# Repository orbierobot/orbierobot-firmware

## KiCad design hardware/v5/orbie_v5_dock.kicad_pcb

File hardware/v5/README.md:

# Orbie V5 electronics (review package)

**Start with `Orbie_V5_Hardware_Review.pdf`** — what was done, how, and the checklist to verify.

| Board | Project | Fab files |
|---|---|---|
| Body controller r0.2 (retrofits the V3 body; outline to be confirmed, see PDF §6) | `orbie_v5_body.kicad_pro` | `out/orbie_v5_body_gerbers.zip`, `_pos.csv`, `_bom_jlc.csv` |
| Belly pogo pad r0.1 | `orbie_v5_pogo.kicad_pro` | `out/orbie_v5_pogo_*` |
| Dock base r0.1 (XIAO ESP32-C3, dead-until-docked pads, IR beacon, feeder/pump driver) | `orbie_v5_dock.kicad_pro` | `out/orbie_v5_dock_*` |
| Feeder module r0.1 | `orbie_v5_feeder.kicad_pro` | `out/orbie_v5_feeder_*` |
| Water module r0.1 | `orbie_v5_water.kicad_pro` | `out/orbie_v5_water_*` |

All five: KiCad 10, 2-layer, autorouted (freerouting), ERC 0 / DRC 0 (`out/*.erc.json`, `out/*.drc.json`).

## Regenerating
The boards are generated from `gen_v5.py` (placement + netlist) using the stock KiCad 10 libraries, then routed by `route_v5.py`:

```
KPY=/Applications/KiCad/KiCad.app/Contents/Frameworks/Python.framework/Versions/3.9/bin/python3
$KPY gen_v5.py . body        # or dock | feeder | water | pogo | all
FREEROUTING=/Applications/freerouting.app/Contents/MacOS/freerouting $KPY route_v5.py orbie_v5_body.kicad_pcb --passes 60
```
Edit the generator, not the outputs. Licence: CERN-OHL-S-2.0.

## Status
Hardware only. Not yet written: RP2040 balance firmware (`orbie_motion`), dock ESP32-C3 firmware, head-side ESP-IDF changes (UART to body on GPIO1/2, IR RMT on GPIO3, lidar UART on GPIO4).

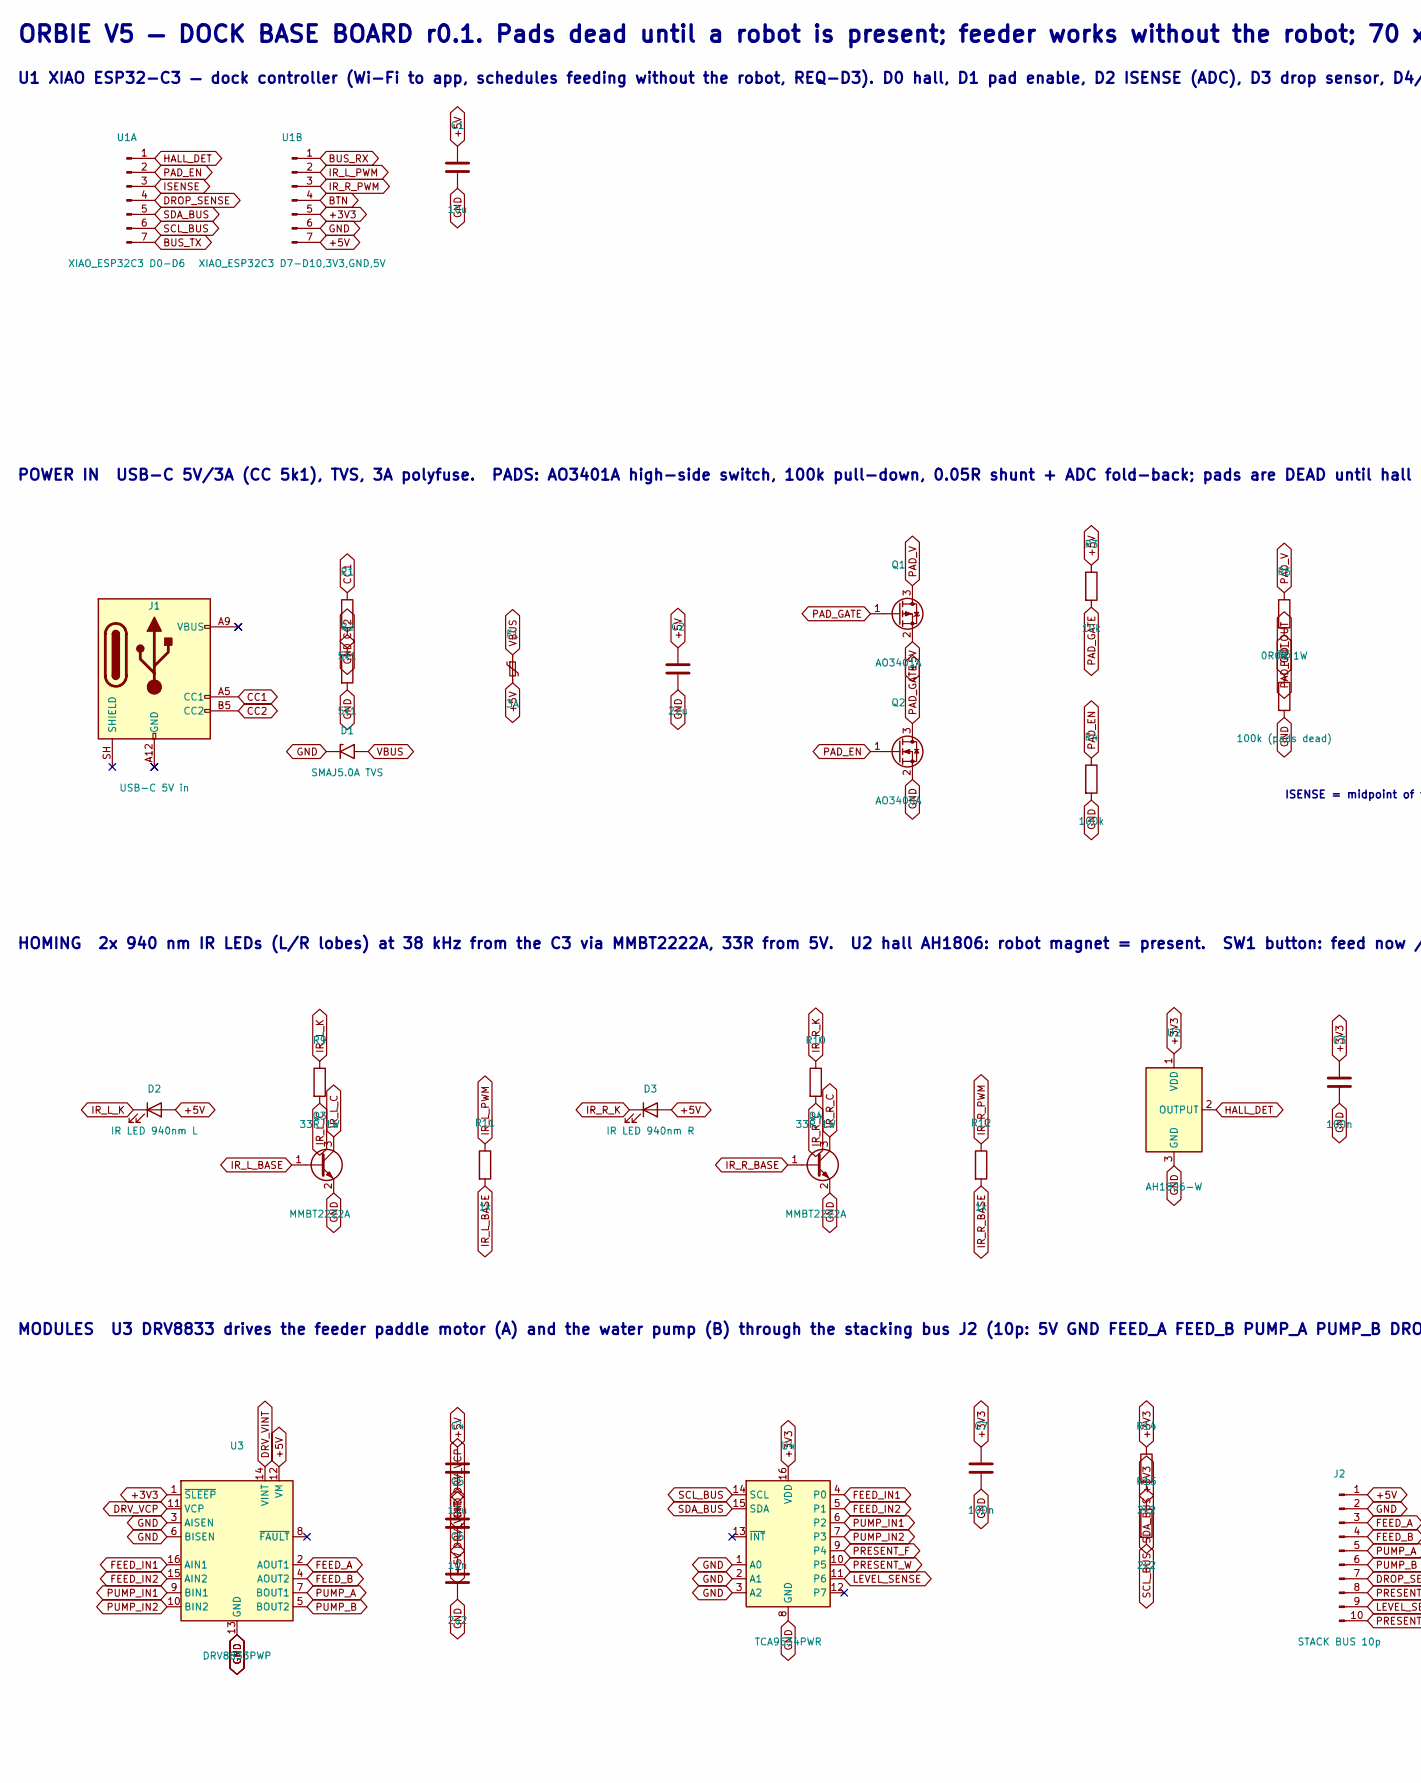
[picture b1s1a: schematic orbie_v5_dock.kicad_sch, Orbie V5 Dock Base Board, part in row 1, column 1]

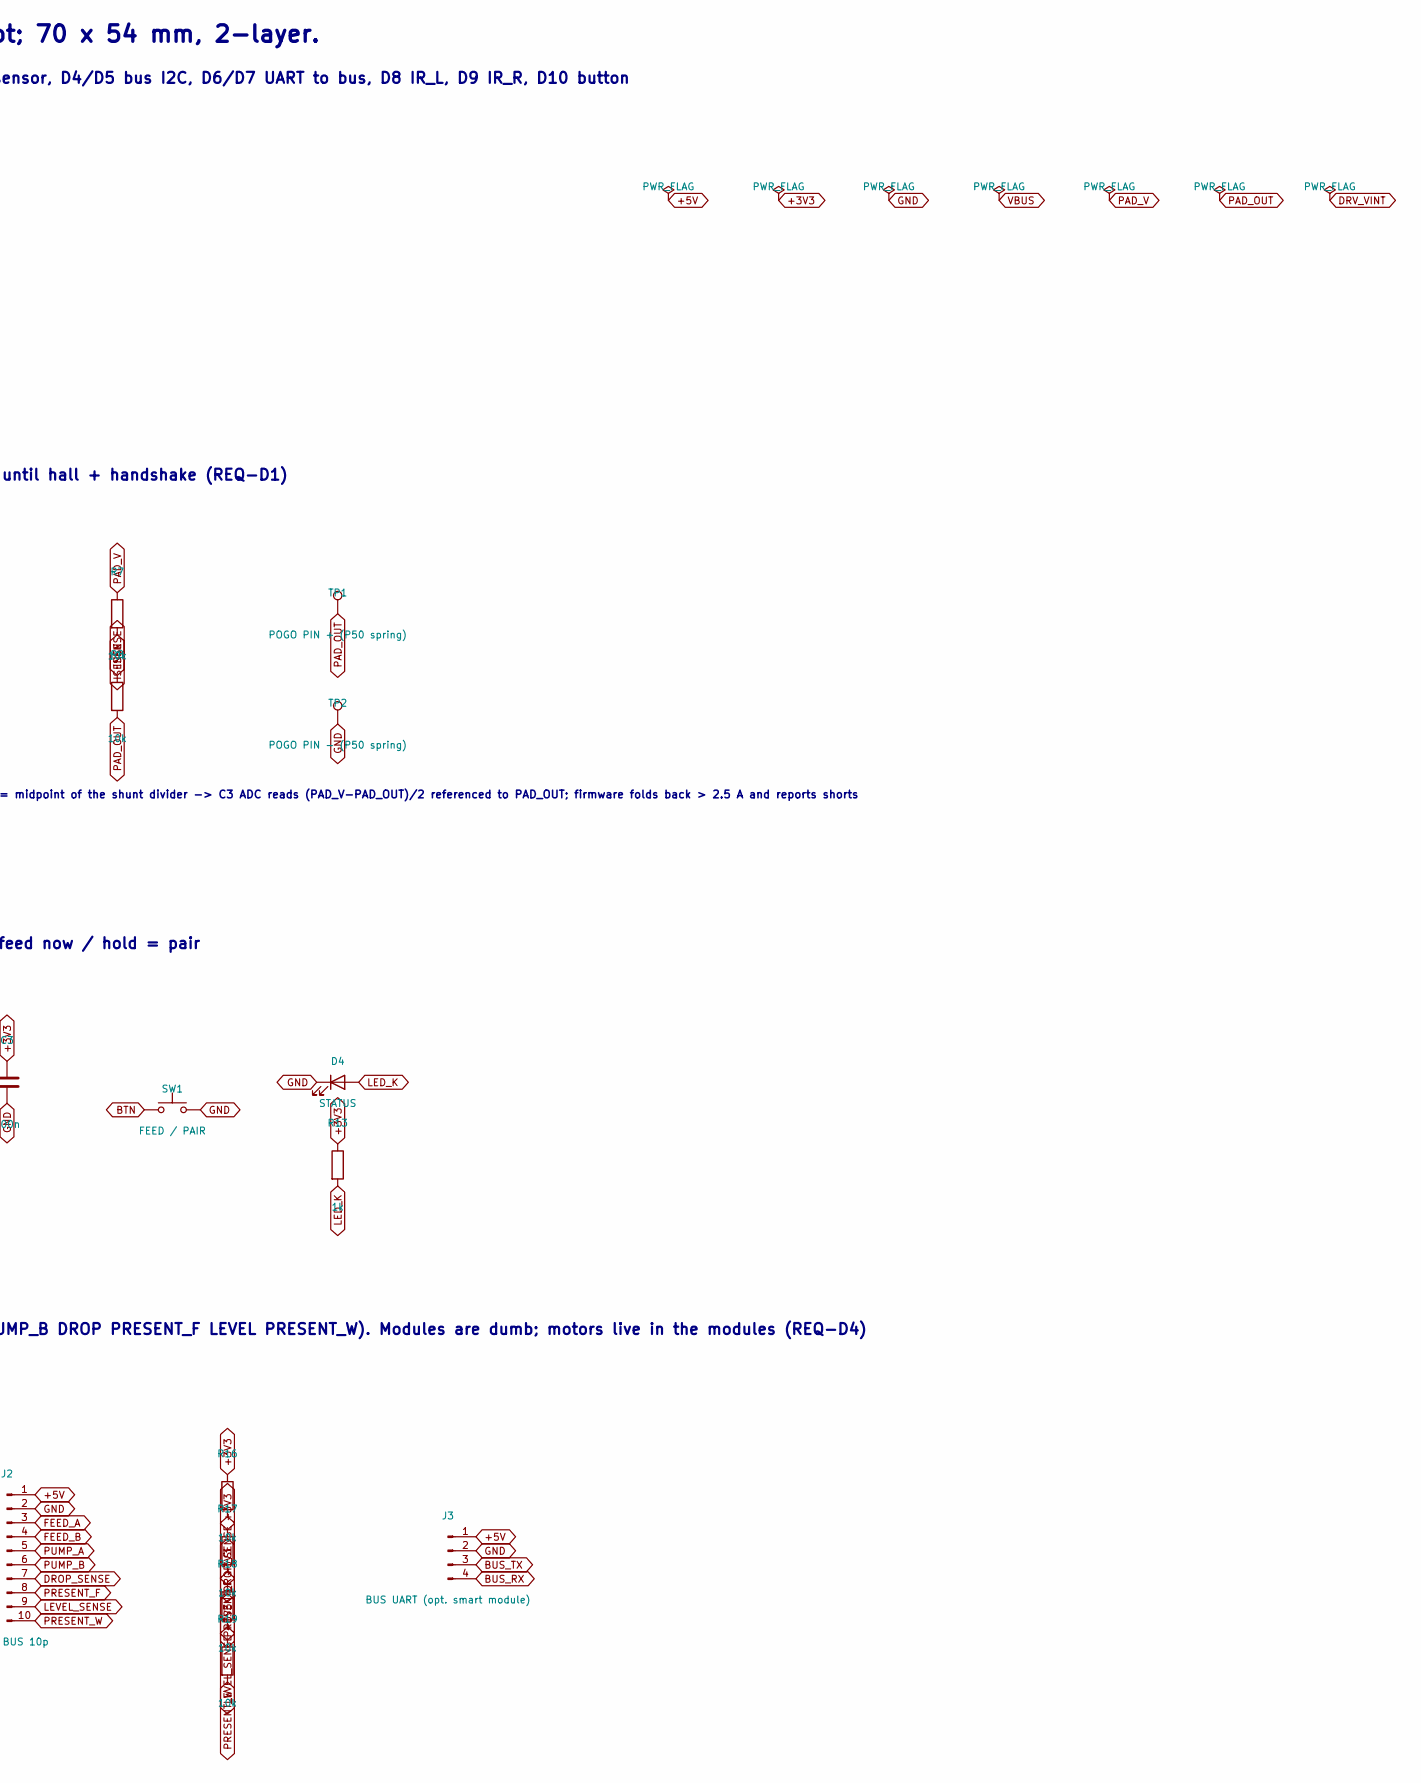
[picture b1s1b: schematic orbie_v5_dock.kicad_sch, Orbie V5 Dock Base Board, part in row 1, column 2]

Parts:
C1, C4: 10u; C_0805_2012Metric_Pad1.18x1.45mm_HandSolder
C2: 22u; C_1210_3225Metric_Pad1.33x2.70mm_HandSolder
C3, C7: 100n; C_0603_1608Metric_Pad1.08x0.95mm_HandSolder
C5: 10n; C_0603_1608Metric_Pad1.08x0.95mm_HandSolder
C6: 2u2; C_0603_1608Metric_Pad1.08x0.95mm_HandSolder
D1: SMAJ5.0A TVS; D_SMA
D2: IR LED 940nm L; LED_D5.0mm
D3: IR LED 940nm R; LED_D5.0mm
D4: STATUS; LED_0603_1608Metric
F1: 3A; Fuse_1206_3216Metric
J1: USB-C 5V in; USB_C_Receptacle_GCT_USB4125-xx-x_6P_TopMnt_Horizontal
J2: STACK BUS 10p; JST_PH_B10B-PH-K_1x10_P2.00mm_Vertical
J3: BUS UART (opt. smart module); JST_PH_B4B-PH-K_1x04_P2.00mm_Vertical
Q1: AO3401A; SOT-23_Handsoldering
Q2: AO3400A; SOT-23_Handsoldering
Q3, Q4: MMBT2222A; SOT-23_Handsoldering
R1, R2: 5k1; R_0603_1608Metric_Pad0.98x0.95mm_HandSolder
R3, R7, R8, R16, R17, R18, R19: 10k; R_0603_1608Metric_Pad0.98x0.95mm_HandSolder
R4: 100k; R_0603_1608Metric_Pad0.98x0.95mm_HandSolder
R5: 0R05 1W; R_2512_6332Metric
R6: 100k (pads dead); R_0603_1608Metric_Pad0.98x0.95mm_HandSolder
R9, R10: 33R 1W; R_1206_3216Metric
R11, R12, R13: 1k; R_0603_1608Metric_Pad0.98x0.95mm_HandSolder
R14, R15: 2k2; R_0603_1608Metric_Pad0.98x0.95mm_HandSolder
SW1: FEED / PAIR; SW_Push_1P1T_NO_CK_KMR2
TP1: POGO PIN + (P50 spring); TestPoint_THTPad_D2.0mm_Drill1.0mm
TP2: POGO PIN - (P50 spring); TestPoint_THTPad_D2.0mm_Drill1.0mm
U1A: XIAO_ESP32C3 D0-D6; XIAO_Castellated
U1B: XIAO_ESP32C3 D7-D10,3V3,GND,5V; XIAO_Castellated
U2: AH1806-W; SOT-23_Handsoldering
U3: DRV8833PWP; HTSSOP-16-1EP_4.4x5mm_P0.65mm_EP3.4x5mm
U4: TCA9534PWR; TSSOP-16_4.4x5mm_P0.65mm

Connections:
+3V3: C3.1, C7.1, R13.1, R14.1, R15.1, R16.1, R17.1, R18.1, R19.1, U1A.12, U1B.5, U2.1 (VDD), U3.1 (~SLEEP), U4.16 (VDD)
+5V: C1.1, C2.1, C4.1, C5.2, D2.2 (A), D3.2 (A), F1.2, J2.1, J3.1, Q1.2 (S), R3.1, U1A.14, U1B.7, U3.12 (VM)
BTN: SW1.1, U1A.11, U1B.4
BUS_RX: J3.4, U1A.8, U1B.1
BUS_TX: J3.3, U1A.7
CC1: J1.A5 (CC1), R1.1
CC2: J1.B5 (CC2), R2.1
DROP_SENSE: J2.7, R16.2, U1A.4
DRV_VCP: C5.1, U3.11 (VCP)
DRV_VINT: C6.1, U3.14 (VINT)
FEED_A: J2.3, U3.2 (AOUT1)
FEED_B: J2.4, U3.4 (AOUT2)
FEED_IN1: U3.16 (AIN1), U4.4 (P0)
FEED_IN2: U3.15 (AIN2), U4.5 (P1)
GND: C1.2, C2.2, C3.2, C4.2, C6.2, C7.2, D1.1 (A1), D4.1 (K), J2.2, J3.2, Q2.2 (S), Q3.2 (E), Q4.2 (E), R1.2, R2.2, R4.2, R6.2, SW1.2, TP2.1, U1A.13, U1B.6, U2.3 (GND), U3.3 (AISEN), U3.6 (BISEN), U3.13 (GND), U3.17 (GND), U4.1 (A0), U4.2 (A1), U4.3 (A2), U4.8 (GND)
HALL_DET: U1A.1, U2.2 (OUTPUT)
IR_L_BASE: Q3.1 (B), R11.2
IR_L_C: Q3.3 (C), R9.2
IR_L_K: D2.1 (K), R9.1
IR_L_PWM: R11.1, U1A.9, U1B.2
IR_R_BASE: Q4.1 (B), R12.2
IR_R_C: Q4.3 (C), R10.2
IR_R_K: D3.1 (K), R10.1
IR_R_PWM: R12.1, U1A.10, U1B.3
ISENSE: R7.2, R8.1, U1A.3
LED_K: D4.2 (A), R13.2
LEVEL_SENSE: J2.9, R18.2, U4.11 (P6)
PAD_EN: Q2.1 (G), R4.1, U1A.2
PAD_GATE: Q1.1 (G), Q2.3 (D), R3.2
PAD_OUT: R5.2, R6.1, R8.2, TP1.1
PAD_V: Q1.3 (D), R5.1, R7.1
PRESENT_F: J2.8, R17.2, U4.9 (P4)
PRESENT_W: J2.10, R19.2, U4.10 (P5)
PUMP_A: J2.5, U3.7 (BOUT1)
PUMP_B: J2.6, U3.5 (BOUT2)
PUMP_IN1: U3.9 (BIN1), U4.6 (P2)
PUMP_IN2: U3.10 (BIN2), U4.7 (P3)
SCL_BUS: R15.2, U1A.6, U4.14 (SCL)
SDA_BUS: R14.2, U1A.5, U4.15 (SDA)
VBUS: D1.2 (A2), F1.1

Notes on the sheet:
ORBIE V5 — DOCK BASE BOARD r0.1. Pads dead until a robot is present; feeder works without the robot; 70 x 54 mm, 2-layer.
U1 XIAO ESP32-C3 — dock controller (Wi-Fi to app, schedules feeding without the robot, REQ-D3). D0 hall, D1 pad enable, D2 ISENSE (ADC), D3 drop sensor, D4/D5 bus I2C, D6/D7 UART to bus, D8 IR_L, D9 IR_R, D10 button
POWER IN USB-C 5V/3A (CC 5k1), TVS, 3A polyfuse. PADS: AO3401A high-side switch, 100k pull-down, 0.05R shunt + ADC fold-back; pads are DEAD until hall + handshake (REQ-D1)
ISENSE = midpoint of the shunt divider -> C3 ADC reads (PAD_V-PAD_OUT)/2 referenced to PAD_OUT; firmware folds back > 2.5 A and reports shorts
HOMING 2x 940 nm IR LEDs (L/R lobes) at 38 kHz from the C3 via MMBT2222A, 33R from 5V. U2 hall AH1806: robot magnet = present. SW1 button: feed now / hold = pair
MODULES U3 DRV8833 drives the feeder paddle motor (A) and the water pump (B) through the stacking bus J2 (10p: 5V GND FEED_A FEED_B PUMP_A PUMP_B DROP PRESENT_F LEVEL PRESENT_W). Modules are dumb; motors live in the modules (REQ-D4)

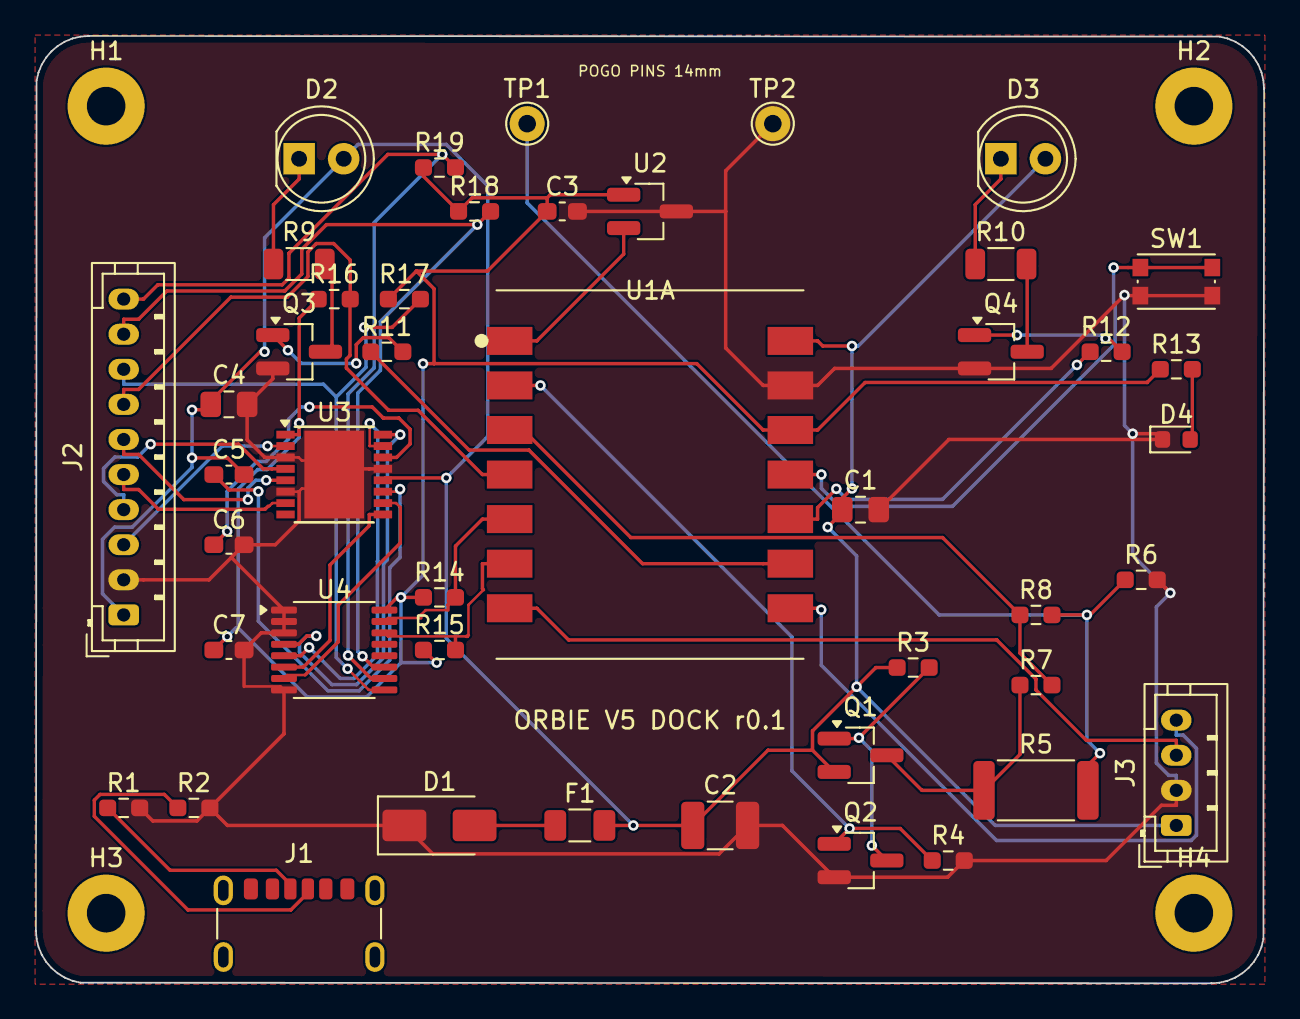
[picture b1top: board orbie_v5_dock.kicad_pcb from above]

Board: 2 copper layers, 70.0 x 54.0 mm, 49 parts (0 on the bottom side), 40 nets.

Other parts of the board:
H1, H2, H3, H4: MountingHole_2.2mm_M2_Pad

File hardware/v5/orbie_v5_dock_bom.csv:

Ref,Value,Symbol,Footprint,Side,Description
U1A,"XIAO_ESP32C3 D0-D6",Connector:Conn_01x07_Pin,orbie_v5:XIAO_Castellated,F,"XIAO ESP32-C3 left row"
U1B,"XIAO_ESP32C3 D7-D10,3V3,GND,5V",Connector:Conn_01x07_Pin,orbie_v5:XIAO_Castellated,F,"XIAO ESP32-C3 right row"
C1,"10u",Device:C,Capacitor_SMD:C_0805_2012Metric_Pad1.18x1.45mm_HandSolder,F,"capacitor"
J1,"USB-C 5V in",Connector:USB_C_Receptacle_PowerOnly_6P,Connector_USB:USB_C_Receptacle_GCT_USB4125-xx-x_6P_TopMnt_Horizontal,F,"USB-C 6P"
R1,"5k1",Device:R,Resistor_SMD:R_0603_1608Metric_Pad0.98x0.95mm_HandSolder,F,"resistor"
R2,"5k1",Device:R,Resistor_SMD:R_0603_1608Metric_Pad0.98x0.95mm_HandSolder,F,"resistor"
D1,"SMAJ5.0A TVS",Diode:SMAJ5.0A,Diode_SMD:D_SMA,F,""
F1,"3A",Device:Polyfuse_Small,Fuse:Fuse_1206_3216Metric,F,""
C2,"22u",Device:C,Capacitor_SMD:C_1210_3225Metric_Pad1.33x2.70mm_HandSolder,F,"capacitor"
Q1,"AO3401A",Transistor_FET:AO3401A,Package_TO_SOT_SMD:SOT-23_Handsoldering,F,"pad high-side switch"
Q2,"AO3400A",Transistor_FET:AO3400A,Package_TO_SOT_SMD:SOT-23_Handsoldering,F,"level shift"
R3,"10k",Device:R,Resistor_SMD:R_0603_1608Metric_Pad0.98x0.95mm_HandSolder,F,"resistor"
R4,"100k",Device:R,Resistor_SMD:R_0603_1608Metric_Pad0.98x0.95mm_HandSolder,F,"resistor"
R5,"0R05 1W",Device:R,Resistor_SMD:R_2512_6332Metric,F,"resistor"
R6,"100k (pads dead)",Device:R,Resistor_SMD:R_0603_1608Metric_Pad0.98x0.95mm_HandSolder,F,"resistor"
R7,"10k",Device:R,Resistor_SMD:R_0603_1608Metric_Pad0.98x0.95mm_HandSolder,F,"resistor"
R8,"10k",Device:R,Resistor_SMD:R_0603_1608Metric_Pad0.98x0.95mm_HandSolder,F,"resistor"
TP1,"POGO PIN + (P50 spring)",Connector:TestPoint,TestPoint:TestPoint_THTPad_D2.0mm_Drill1.0mm,F,"spring pin, 14 mm pitch"
TP2,"POGO PIN - (P50 spring)",Connector:TestPoint,TestPoint:TestPoint_THTPad_D2.0mm_Drill1.0mm,F,"spring pin"
D2,"IR LED 940nm L",Device:LED,LED_THT:LED_D5.0mm,F,"beacon lobe"
R9,"33R 1W",Device:R,Resistor_SMD:R_1206_3216Metric,F,"resistor"
Q3,"MMBT2222A",Transistor_BJT:MMBT2222A,Package_TO_SOT_SMD:SOT-23_Handsoldering,F,"LED driver"
R11,"1k",Device:R,Resistor_SMD:R_0603_1608Metric_Pad0.98x0.95mm_HandSolder,F,"resistor"
D3,"IR LED 940nm R",Device:LED,LED_THT:LED_D5.0mm,F,"beacon lobe"
R10,"33R 1W",Device:R,Resistor_SMD:R_1206_3216Metric,F,"resistor"
Q4,"MMBT2222A",Transistor_BJT:MMBT2222A,Package_TO_SOT_SMD:SOT-23_Handsoldering,F,"LED driver"
R12,"1k",Device:R,Resistor_SMD:R_0603_1608Metric_Pad0.98x0.95mm_HandSolder,F,"resistor"
U2,"AH1806-W",Sensor_Magnetic:AH1806-W,Package_TO_SOT_SMD:SOT-23_Handsoldering,F,"hall: robot present"
C3,"100n",Device:C,Capacitor_SMD:C_0603_1608Metric_Pad1.08x0.95mm_HandSolder,F,"capacitor"
SW1,"FEED / PAIR",Switch:SW_Push,Button_Switch_SMD:SW_Push_1P1T_NO_CK_KMR2,F,"user button"
D4,"STATUS",Device:LED,LED_SMD:LED_0603_1608Metric,F,""
R13,"1k",Device:R,Resistor_SMD:R_0603_1608Metric_Pad0.98x0.95mm_HandSolder,F,"resistor"
U3,"DRV8833PWP",Driver_Motor:DRV8833PWP,Package_SO:HTSSOP-16-1EP_4.4x5mm_P0.65mm_EP3.4x5mm,F,"feeder + pump driver"
C4,"10u",Device:C,Capacitor_SMD:C_0805_2012Metric_Pad1.18x1.45mm_HandSolder,F,"capacitor"
C5,"10n",Device:C,Capacitor_SMD:C_0603_1608Metric_Pad1.08x0.95mm_HandSolder,F,"capacitor"
C6,"2u2",Device:C,Capacitor_SMD:C_0603_1608Metric_Pad1.08x0.95mm_HandSolder,F,"capacitor"
U4,"TCA9534PWR",Interface_Expansion:TCA9534,Package_SO:TSSOP-16_4.4x5mm_P0.65mm,F,"expander: motor inputs + module present"
C7,"100n",Device:C,Capacitor_SMD:C_0603_1608Metric_Pad1.08x0.95mm_HandSolder,F,"capacitor"
R14,"2k2",Device:R,Resistor_SMD:R_0603_1608Metric_Pad0.98x0.95mm_HandSolder,F,"resistor"
R15,"2k2",Device:R,Resistor_SMD:R_0603_1608Metric_Pad0.98x0.95mm_HandSolder,F,"resistor"
J2,"STACK BUS 10p",Connector:Conn_01x10_Pin,Connector_JST:JST_PH_B10B-PH-K_1x10_P2.00mm_Vertical,F,"to feeder / water modules (spring contacts on the deck)"
R16,"10k",Device:R,Resistor_SMD:R_0603_1608Metric_Pad0.98x0.95mm_HandSolder,F,"resistor"
R17,"10k",Device:R,Resistor_SMD:R_0603_1608Metric_Pad0.98x0.95mm_HandSolder,F,"resistor"
R18,"10k",Device:R,Resistor_SMD:R_0603_1608Metric_Pad0.98x0.95mm_HandSolder,F,"resistor"
R19,"10k",Device:R,Resistor_SMD:R_0603_1608Metric_Pad0.98x0.95mm_HandSolder,F,"resistor"
J3,"BUS UART (opt. smart module)",Connector:Conn_01x04_Pin,Connector_JST:JST_PH_B4B-PH-K_1x04_P2.00mm_Vertical,F,"optional"

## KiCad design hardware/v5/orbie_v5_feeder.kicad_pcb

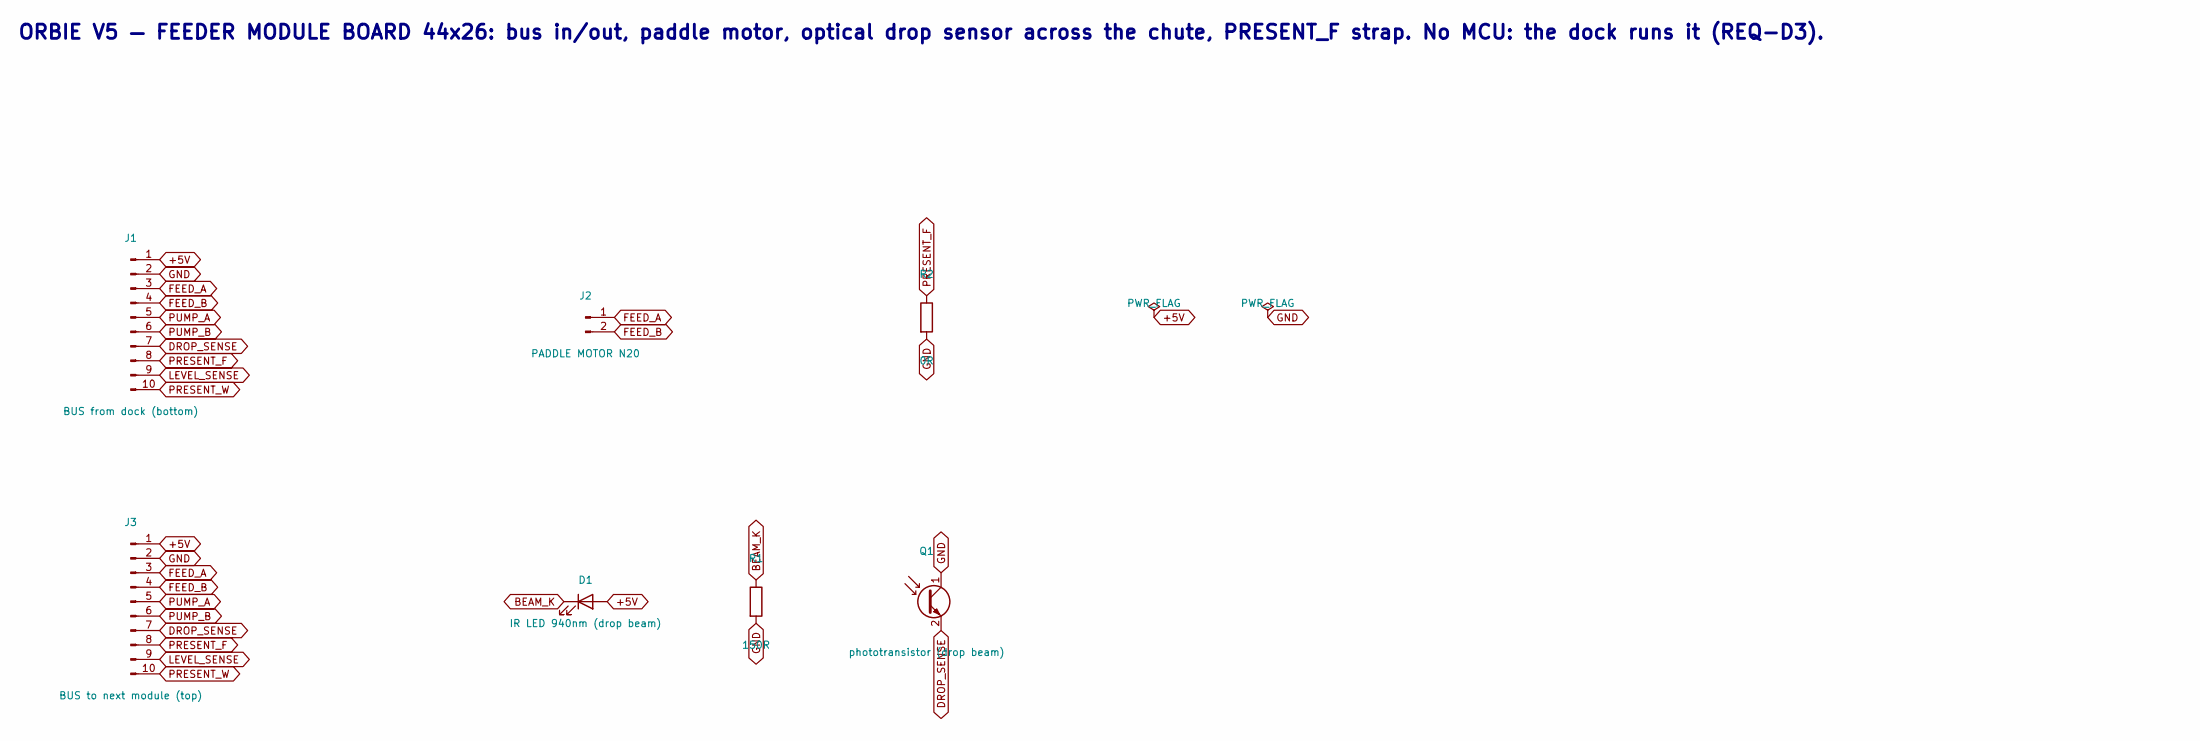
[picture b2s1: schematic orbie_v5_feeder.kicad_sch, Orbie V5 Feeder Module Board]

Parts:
D1: IR LED 940nm (drop beam); LED_D3.0mm
J1: BUS from dock (bottom); JST_PH_B10B-PH-K_1x10_P2.00mm_Vertical
J2: PADDLE MOTOR N20; JST_PH_B2B-PH-K_1x02_P2.00mm_Vertical
J3: BUS to next module (top); JST_PH_B10B-PH-K_1x10_P2.00mm_Vertical
Q1: phototransistor (drop beam); LED_D3.0mm
R1: 150R; R_0603_1608Metric_Pad0.98x0.95mm_HandSolder
R2: 0R; R_0603_1608Metric_Pad0.98x0.95mm_HandSolder

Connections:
+5V: D1.2 (A), J1.1, J3.1
BEAM_K: D1.1 (K), R1.1
DROP_SENSE: J1.7, J3.7, Q1.2 (E)
FEED_A: J1.3, J2.1, J3.3
FEED_B: J1.4, J2.2, J3.4
GND: J1.2, J3.2, Q1.1 (C), R1.2, R2.2
LEVEL_SENSE: J1.9, J3.9
PRESENT_F: J1.8, J3.8, R2.1
PRESENT_W: J1.10, J3.10
PUMP_A: J1.5, J3.5
PUMP_B: J1.6, J3.6

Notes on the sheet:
ORBIE V5 — FEEDER MODULE BOARD 44x26: bus in/out, paddle motor, optical drop sensor across the chute, PRESENT_F strap. No MCU: the dock runs it (REQ-D3).

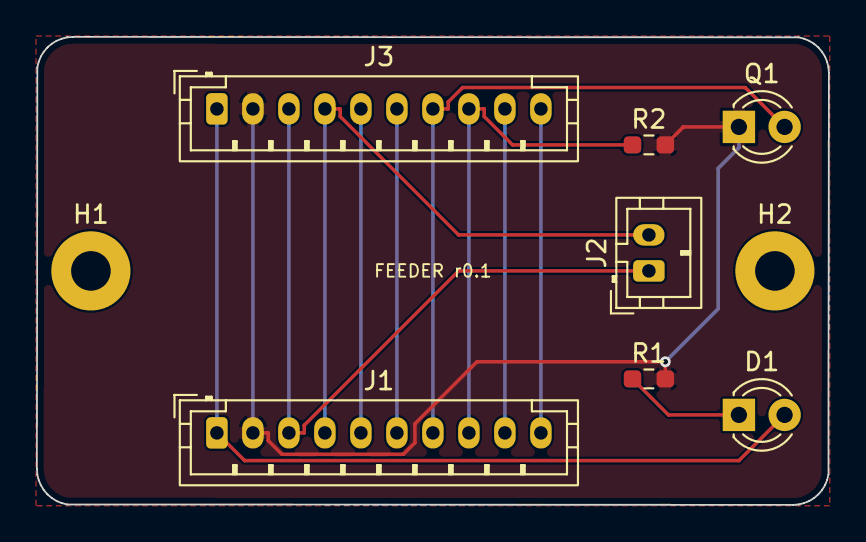
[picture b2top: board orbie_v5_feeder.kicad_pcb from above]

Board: 2 copper layers, 44.0 x 26.0 mm, 9 parts (0 on the bottom side), 11 nets.

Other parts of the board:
H1, H2: MountingHole_2.2mm_M2_Pad

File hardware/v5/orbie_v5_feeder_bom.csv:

Ref,Value,Symbol,Footprint,Side,Description
J1,"BUS from dock (bottom)",Connector:Conn_01x10_Pin,Connector_JST:JST_PH_B10B-PH-K_1x10_P2.00mm_Vertical,F,"spring-contact bus, bottom face"
J3,"BUS to next module (top)",Connector:Conn_01x10_Pin,Connector_JST:JST_PH_B10B-PH-K_1x10_P2.00mm_Vertical,F,"pass-through so the water tower stacks on top"
J2,"PADDLE MOTOR N20",Connector:Conn_01x02_Pin,Connector_JST:JST_PH_B2B-PH-K_1x02_P2.00mm_Vertical,F,"paddle drum gearmotor"
D1,"IR LED 940nm (drop beam)",Device:LED,LED_THT:LED_D3.0mm,F,"chute emitter"
R1,"150R",Device:R,Resistor_SMD:R_0603_1608Metric_Pad0.98x0.95mm_HandSolder,F,"resistor"
Q1,"phototransistor (drop beam)",Device:Q_Photo_NPN,LED_THT:LED_D3.0mm,F,"chute receiver, pulled up at the dock"
R2,"0R",Device:R,Resistor_SMD:R_0603_1608Metric_Pad0.98x0.95mm_HandSolder,F,"resistor"

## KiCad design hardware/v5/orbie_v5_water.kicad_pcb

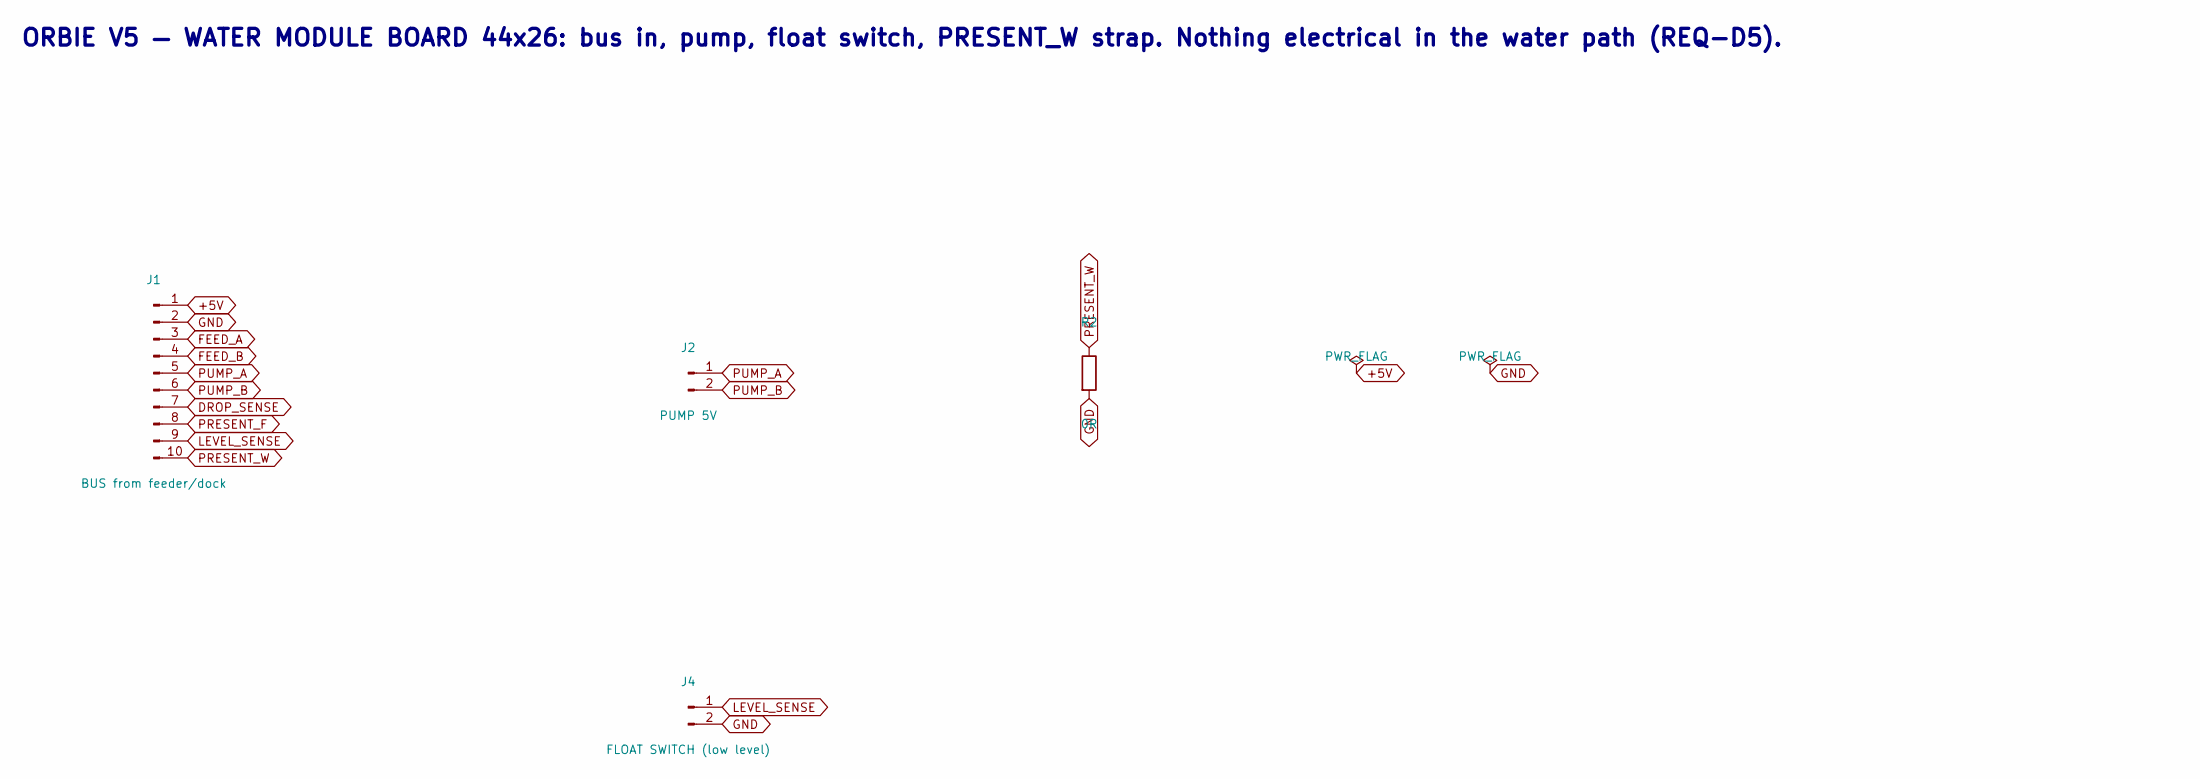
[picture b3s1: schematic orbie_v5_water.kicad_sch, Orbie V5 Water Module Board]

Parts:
J1: BUS from feeder/dock; JST_PH_B10B-PH-K_1x10_P2.00mm_Vertical
J2: PUMP 5V; JST_PH_B2B-PH-K_1x02_P2.00mm_Vertical
J4: FLOAT SWITCH (low level); JST_PH_B2B-PH-K_1x02_P2.00mm_Vertical
R2: 0R; R_0603_1608Metric_Pad0.98x0.95mm_HandSolder

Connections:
+5V: J1.1
DROP_SENSE: J1.7
FEED_A: J1.3
FEED_B: J1.4
GND: J1.2, J4.2, R2.2
LEVEL_SENSE: J1.9, J4.1
PRESENT_F: J1.8
PRESENT_W: J1.10, R2.1
PUMP_A: J1.5, J2.1
PUMP_B: J1.6, J2.2

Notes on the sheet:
ORBIE V5 — WATER MODULE BOARD 44x26: bus in, pump, float switch, PRESENT_W strap. Nothing electrical in the water path (REQ-D5).

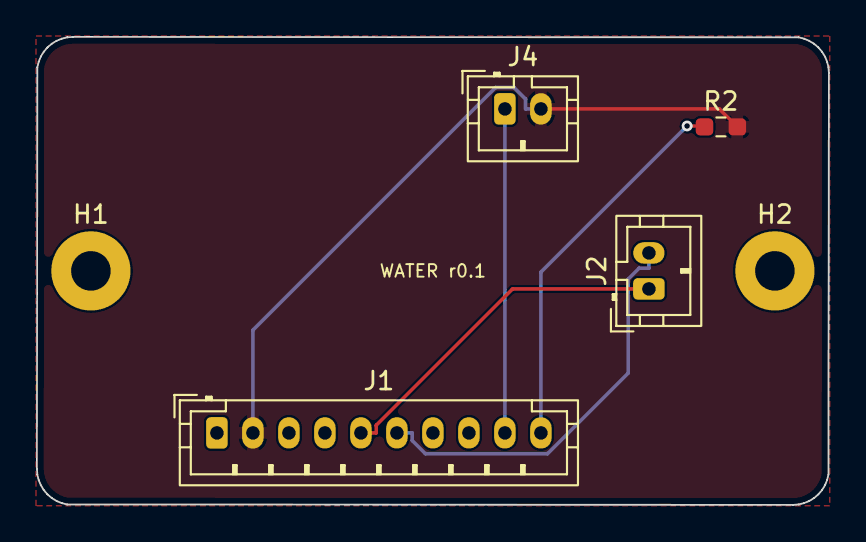
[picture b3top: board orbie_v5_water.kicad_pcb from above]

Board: 2 copper layers, 44.0 x 26.0 mm, 6 parts (0 on the bottom side), 5 nets.

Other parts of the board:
H1, H2: MountingHole_2.2mm_M2_Pad

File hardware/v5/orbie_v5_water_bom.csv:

Ref,Value,Symbol,Footprint,Side,Description
J1,"BUS from feeder/dock",Connector:Conn_01x10_Pin,Connector_JST:JST_PH_B10B-PH-K_1x10_P2.00mm_Vertical,F,"spring-contact bus, bottom face"
J2,"PUMP 5V",Connector:Conn_01x02_Pin,Connector_JST:JST_PH_B2B-PH-K_1x02_P2.00mm_Vertical,F,"submersible pump"
J4,"FLOAT SWITCH (low level)",Connector:Conn_01x02_Pin,Connector_JST:JST_PH_B2B-PH-K_1x02_P2.00mm_Vertical,F,"closes when reservoir low"
R2,"0R",Device:R,Resistor_SMD:R_0603_1608Metric_Pad0.98x0.95mm_HandSolder,F,"resistor"

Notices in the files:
hardware/v5/orbie_v5_body.kicad_sch:
Orbie / Ayva Labs — CERN-OHL-S-2.0
